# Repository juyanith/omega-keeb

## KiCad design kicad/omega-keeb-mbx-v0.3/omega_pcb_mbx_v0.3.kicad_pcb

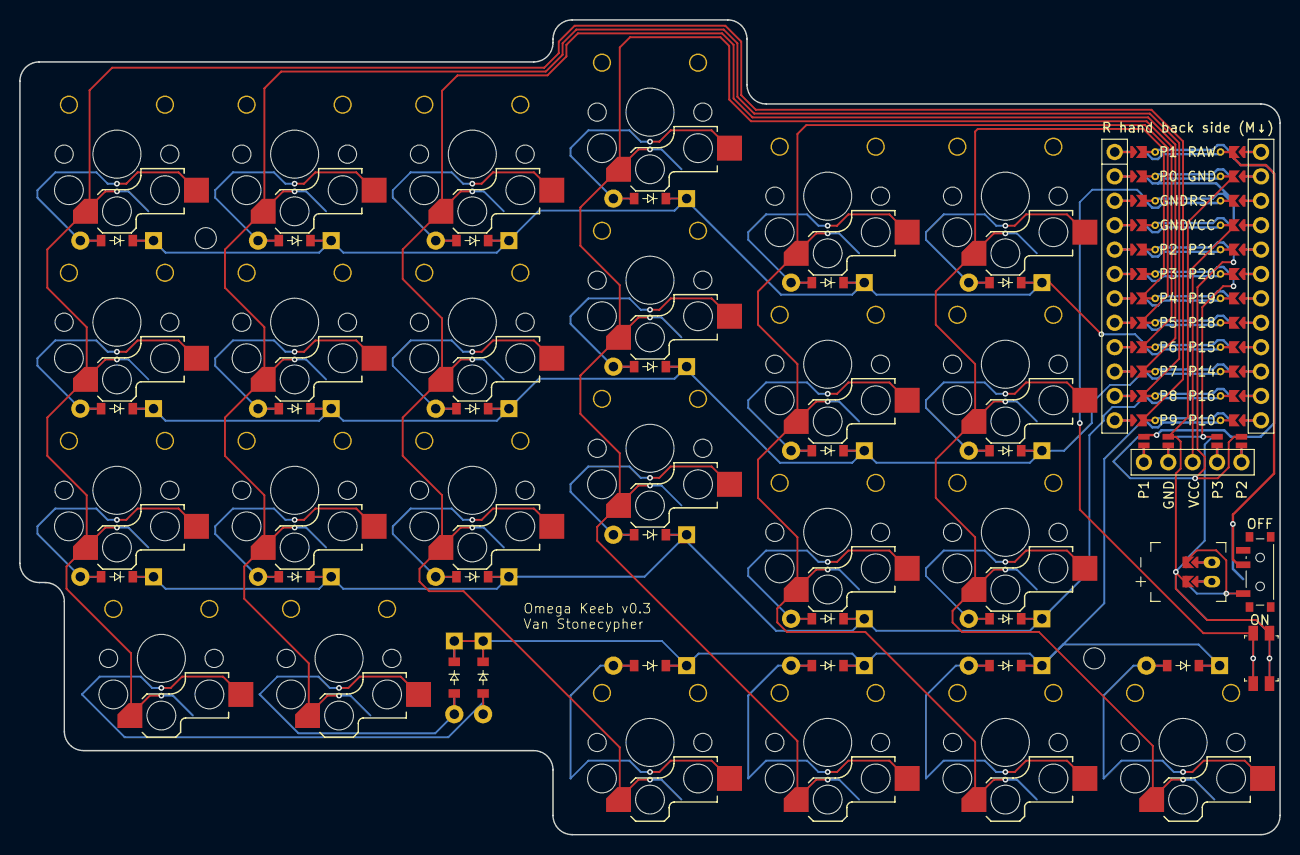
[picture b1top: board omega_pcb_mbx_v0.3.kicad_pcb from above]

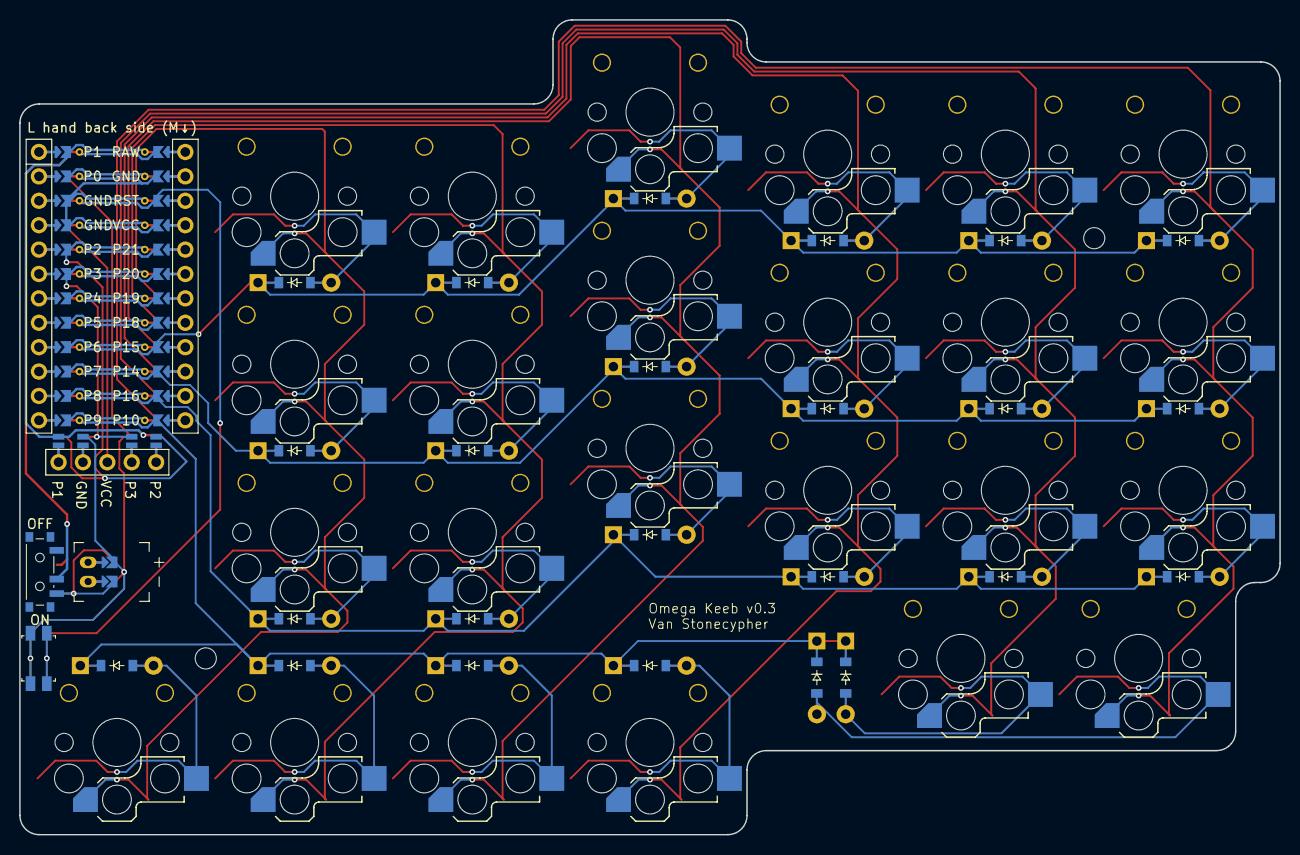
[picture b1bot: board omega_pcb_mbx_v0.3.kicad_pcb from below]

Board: 2 copper layers, 131.2 x 84.8 mm, 55 parts (28 on the bottom side), 48 nets.

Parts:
D1, D2, D3, D4, D5, D6, D7, D8, D9, D10, D11, D12, D13, D14, D15, D16, D17, D18, D19, D20, D21, D22, D23, D24: ComboDiode
DISP1: display_nice_view
JST1: battery_connector_jst_ph_2
MCU1: mcu_nice_nano
MH1, MH2: mounting_hole_npth
PWR1: power_switch_smd_side
RST1: reset_switch_smd_side
S1, S2, S3, S4, S5, S6, S7, S8, S9, S10, S11, S12, S13, S14, S15, S16, S17, S18, S19, S20, S21, S22, S23, S24: switch_choc_v1_v2

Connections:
BAT_P: JST1.1, PWR1.1, PWR1.3
DISP1_1: DISP1.1, DISP1.10, DISP1.23
DISP1_2: DISP1.2, DISP1.11, DISP1.22
DISP1_4: DISP1.4, DISP1.12, DISP1.21
DISP1_5: DISP1.5, DISP1.13, DISP1.20
GND: DISP1.15, DISP1.25, JST1.2, MCU1.102, MCU1.121, MCU1.122, RST1.1, RST1.3
JST1_1: JST1.11, JST1.21, JST1.31
JST1_2: JST1.12, JST1.22, JST1.32
P1: DISP1.14, DISP1.24, MCU1.124
P2: DISP1.17, DISP1.27, MCU1.120
P3: DISP1.16, DISP1.26, MCU1.119
P4: MCU1.118, S16.1, S17.1, S18.1, S24.1
P5: MCU1.117, S13.1, S14.1, S15.1, S23.1
P6: MCU1.116, S10.1, S11.1, S12.1, S22.1
P7: MCU1.115, S7.1, S8.1, S9.1, S21.1
P8: MCU1.114, S4.1, S5.1, S6.1, S20.1
P9: MCU1.113, S1.1, S2.1, S3.1, S19.1
P10: D19.1, D20.1, D21.1, D22.1, D23.1, D24.1, MCU1.112
P14: D2.1, D5.1, D8.1, D11.1, D14.1, D17.1, MCU1.110
P15: D3.1, D6.1, D9.1, D12.1, D15.1, D18.1, MCU1.109
P16: D1.1, D4.1, D7.1, D10.1, D13.1, D16.1, MCU1.111
RAW: MCU1.101, PWR1.2
RST: MCU1.103, RST1.2, RST1.4
VCC: DISP1.3, MCU1.104
fifth_only: D21.2, S23.2
first_only: D23.2, S19.2
fourth_only: D20.2, S22.2
index_bottom: D13.2, S13.2
index_home: D14.2, S14.2
index_top: D15.2, S15.2
inner_bottom: D16.2, S16.2
inner_home: D17.2, S17.2
inner_top: D18.2, S18.2
middle_bottom: D10.2, S10.2
middle_home: D11.2, S11.2
middle_top: D12.2, S12.2
outer_bottom: D1.2, S1.2
outer_home: D2.2, S2.2
outer_top: D3.2, S3.2
pinky_bottom: D4.2, S4.2
pinky_home: D5.2, S5.2
pinky_top: D6.2, S6.2
ring_bottom: D7.2, S7.2
ring_home: D8.2, S8.2
ring_top: D9.2, S9.2
second_only: D24.2, S20.2
sixth_only: D22.2, S24.2
third_only: D19.2, S21.2

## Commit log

2025-01-01 Added ergogen config.yaml
2025-01-01 Added mountinhole.js
2025-01-01 Added footprints for xiao boards
2025-01-01 Updated config.yaml
2025-01-01 Added promicro.js
2025-01-01 Working on pcb layout some more
2025-01-03 Added rev_nano from Janus Keyboard.
2025-01-03 Updated pcb to be reversable.
2025-01-03 Created modified version of rev_nano.js that includes B- and B+.
2025-01-03 Updated config.yaml to use rev_nano_batt.
2025-01-03 Added rev_jstph.js and rev_slider.js
2025-01-03 Added niceview and rev_button.
2025-01-03 Moved old ergogen dir
2025-01-04 Updated to use ceoloide footprints, and back to reversible mb.
2025-01-04 Changed back to MBK keycap spacing and reworked layout.
2025-01-05 Fixed added 1mm between keys and adjusted outer edges.
2025-01-05 Added v0.2 files.
2025-01-05 Fixed name errors.
2025-01-05 Fixed file name extension.
2025-01-05 Added v0.2 gerber files.
2025-01-05 Added omega-keeb-mbx-v0.2.zip
2025-01-05 Created separate kicad directory.
2025-01-05 Moved ergogen files into mbx directory.
2025-01-05 Moved original files to appropriate directory.
2025-01-05 Moved original files again.
2025-01-05 Added a bit more space between keys.
2025-01-06 Added gerbers for v0.3
2025-01-06 Added v0.3 kicad files.
2025-01-06 Updated outside dimensions.
2025-01-06 Fixed outside lower section.
2025-01-10 Added .DS_Store to .gitignore.
